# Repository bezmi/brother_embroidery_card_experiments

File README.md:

# Brother embroidery card experiments
I wanted to try and get an old Brother NV500D working with own digitised PES files.

These machines have only got a proprietary memory card slot, which takes brother design cards.

Rewritable cards were available from many manufacturers, including Brother, but they've since mostly fizzled away as the newer machines have USB on board.

This repository is my documentation for a custom design card PCB and software to write images to these cards.

## The PCB
The brother design cards use parallel memory ICs, with 19 address pins and 8 data pins.
My initial experimental PCB is based on the [esp32 PCB done by AeroX2](https://github.com/AeroX2/brother-cart-emulator), but uses a Teensy 3.5 because that's what I had lying around - lots of 5V tolerant GPIO so I didn't need to order shift register/buffer ICs.

### Teensy firmware
The teensy firmware is pretty clunky right now. It's based on AeroX2's nicer esp32 firmware.

## Generating images and programming the flash

This pretty clunky right now because I'm just trying to get it to work and hopefully get a custom program written to create the binary image to be loaded onto the flash.
First, use [AeroX2's image-dumper'](https://github.com/AeroX2/brother-cart-emulator/tree/main/image-dumper) or my modified version of [mlueft's vikant emulator](https://github.com/mlueft/emcr/tree/master/emulators/vikantUltimateBox) to create an `image.bin` from a `PEC` or `PES` file.
Place `image.bin` on a micro SD card (make sure it is named image.bin).

Plug the Teensy into the memory card PCB, and the SD card into the Teensy and issue a "W" command via a serial monitor.
You can use "V" to verify that the file written to the flash chip matches the `image.bin` on the SD card.

**NOTE: DO NOT HAVE THE MEMORY CARD PLUGGED INTO THE MACHINE POWERED ON AT THE SAME TIME AS HAVING THE TEENSY PLUGGED IN AND CONNECTED VIA USB. THIS BOARD CURRENTLY HAS 0 SAFETY GUARANTEES AND YOU WILL POSSIBLY EXPLODE THE TEENSY**

### Using the Vikant software
Unfortunately I haven't got this part working on linux yet, so I begrudgingly boot into Windows until our own software to write to the cards is created.

1. Download and install the old [Vikant Ultimate Box serial port](http://vikant-emb.com/downloads1/UltimateExplorerInstallation.exe) software (the previous link is the direct download. [Go the bottom of this page if it doesn't work.](https://vikant-emb.com/downloads)).
2. Download and install [`com0com`](https://com0com.sourceforge.net/).
3. Edit the `main.py` in the `card_emulator` directory to use one of the COM ports created with com0com (use device manager to figure it out). 
4. Assuming you have python installed, start an administrator command prompt and `cd` to the folder containing `main.py`.
5. Run python `main.py`.
6. Start the UltimateExplorer (Brother) software. It should detect a card on a COM port and let you write files.
7. Copy `image.bin` from the `card_emulator` directory to the microSD card and follow the instructions above to get it written to the memory card.

#### Dirty hacks
Eventually, there will be a direct pipeline from PES file -> python -> directly written to the flash memory.
At the moment, I have just edited mlueft's code to create a 512K data file to match our flash chip.
Vikant still thinks it's a 1024K chip, so if you write more than 512K worth of data, it will cause issues.

## Experiments
I am trying to figure out the format of the binary data written to the brother embroidery card.
[This EEVblog forum post](https://www.eevblog.com/forum/reviews/brother-(possibly-also-bernina)-embroidery-machine-memory-cards/) was very helpful and is what initially introduced me to AeroX2's stuff. There is a wealth of information in that thread.

The `experiments.ipynb` jupyter notebook contains an interactive plotting routine that will go through the `image.bin` file and plot the data as a bitmap. I did this to figure out where and what thumbnails are stored on the card.

The stitch data is stored at the very end of the card, with thumbnails for the embroidery patterns stored before that.

There are also many random thumbnails in lots of languages for UI elements. It appears that the embroidery card also stores the UI for anything inside the "design card menu" from the LCD screen of the machine - probably thanks to the limited storage these old machines had.

Many of the elements of a standard PEC file are present in this file, but the order is different.

The main thing we need to figure out is where the values which point to the start of the stitch data and thumbnails for each PES file written to the card are stored.

# Reverse engineering the file structure
See [notes.org](notes.org)

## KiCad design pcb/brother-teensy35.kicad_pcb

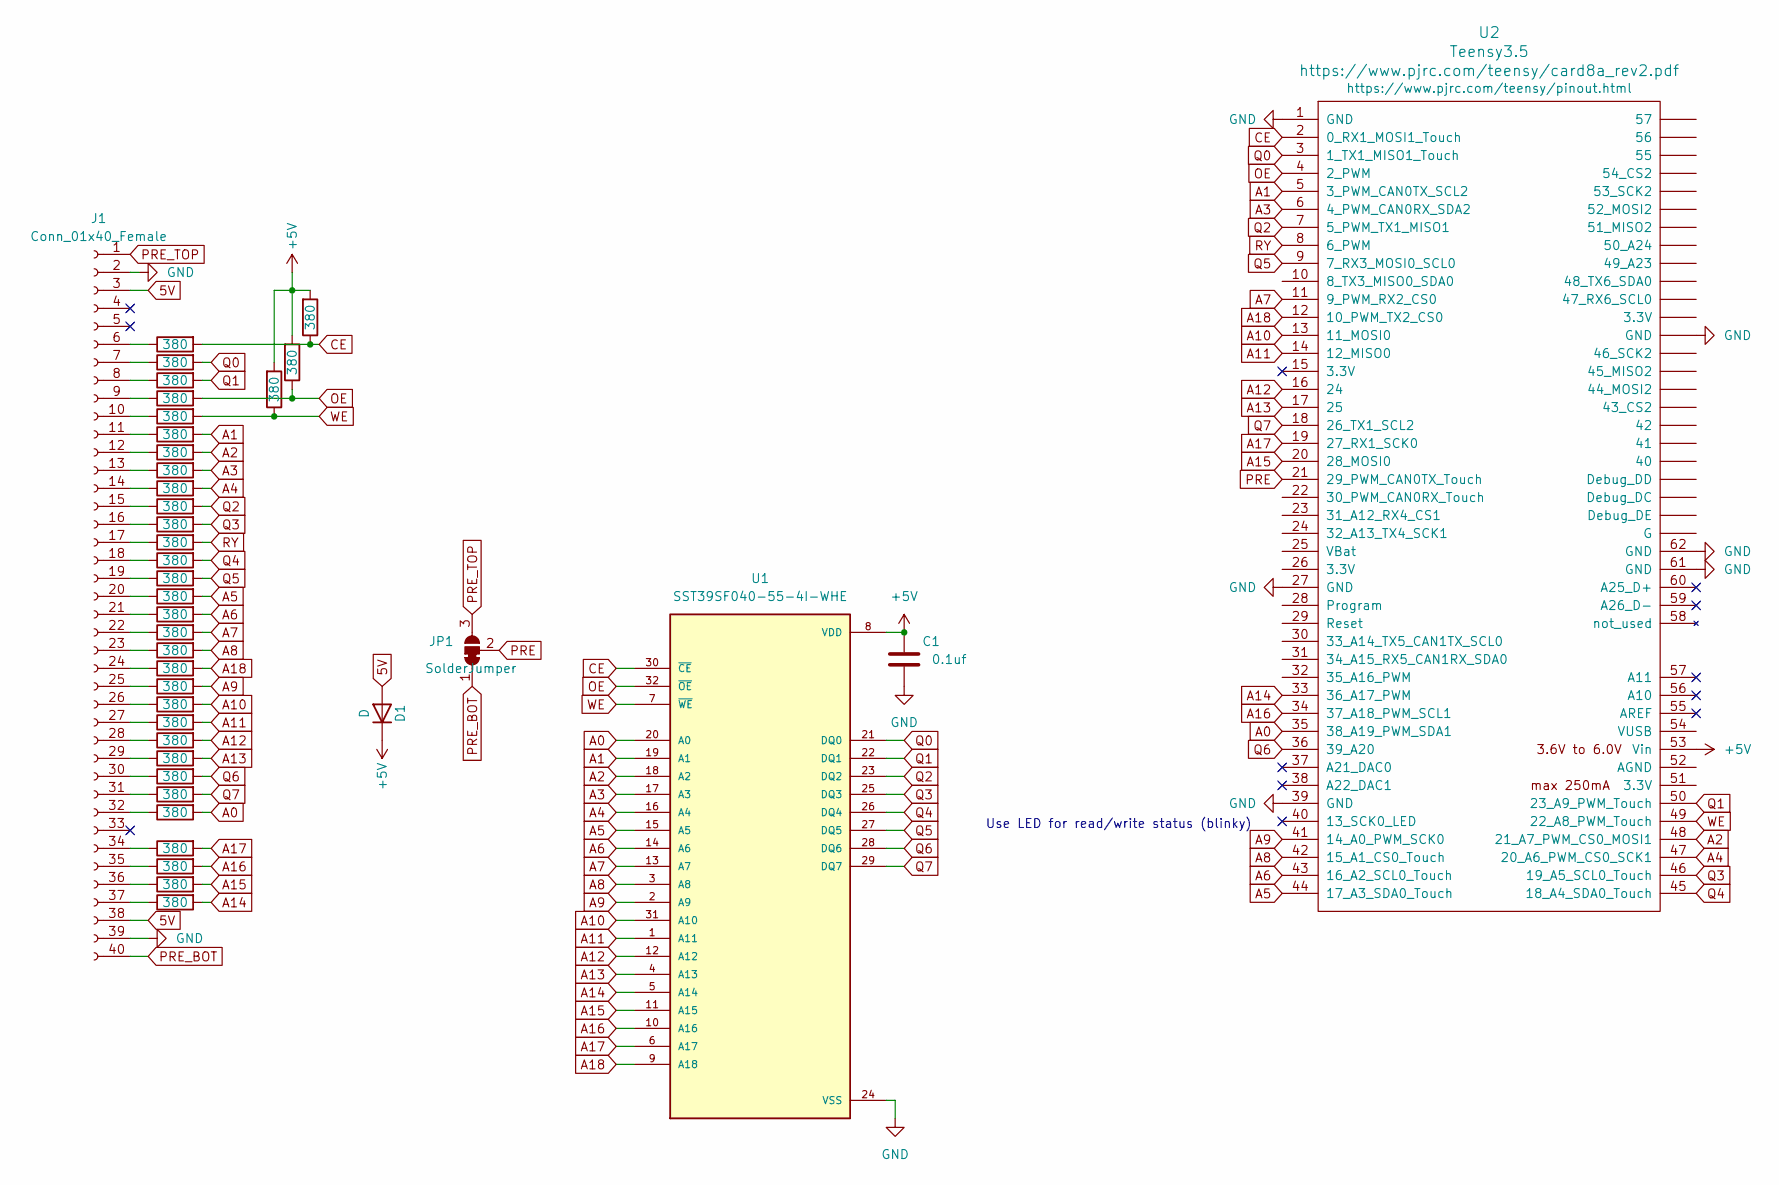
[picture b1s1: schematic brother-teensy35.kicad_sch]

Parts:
C1: 0.1uf; C_0603_1608Metric_Pad1.08x0.95mm_HandSolder
D1: D; D_SOD-323_HandSoldering
J1: Conn_01x40_Female; PinHeader_1x40_SMD
JP1: SolderJumper; SolderJumper-3_P1.3mm_Bridged12_Pad1.0x1.5mm
R1, R2, R3, R4, R5, R6, R7, R8, R9, R10, R11, R12, R13, R14, R15, R16, R17, R18, R19, R20, R21, R22, R23, R24, R25, R26, R27, R28, R29, R30, R31, R32, R33, R34: 380; R_0603_1608Metric_Pad0.98x0.95mm_HandSolder
U1: SST39SF040-55-4I-WHE; SOP50P1400X120-32N; PARTREV C
U2: Teensy3.5; Teensy35_36

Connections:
5V: D1.2 (A), J1.3, J1.38
+5V: C1.2, D1.1 (K), R32.2, R33.2, R34.2, U1.8 (VDD), U2.53 (Vin)
A0: R27.2, U1.20 (A0), U2.35 (38_A19_PWM_SDA1)
A1: R6.2, U1.19 (A1), U2.5 (3_PWM_CAN0TX_SCL2)
A2: R7.2, U1.18 (A2), U2.48 (21_A7_PWM_CS0_MOSI1)
A3: R8.2, U1.17 (A3), U2.6 (4_PWM_CAN0RX_SDA2)
A4: R9.2, U1.16 (A4), U2.47 (20_A6_PWM_CS0_SCK1)
A5: R15.2, U1.15 (A5), U2.44 (17_A3_SDA0_Touch)
A6: R16.2, U1.14 (A6), U2.43 (16_A2_SCL0_Touch)
A7: R17.2, U1.13 (A7), U2.11 (9_PWM_RX2_CS0)
A8: R18.2, U1.3 (A8), U2.42 (15_A1_CS0_Touch)
A9: R20.2, U1.2 (A9), U2.41 (14_A0_PWM_SCK0)
A10: R21.2, U1.31 (A10), U2.13 (11_MOSI0)
A11: R22.2, U1.1 (A11), U2.14 (12_MISO0)
A12: R23.2, U1.12 (A12), U2.16 (24)
A13: R24.2, U1.4 (A13), U2.17 (25)
A14: R31.2, U1.5 (A14), U2.33 (36_A17_PWM)
A15: R30.2, U1.11 (A15), U2.20 (28_MOSI0)
A16: R29.2, U1.10 (A16), U2.34 (37_A18_PWM_SCL1)
A17: R28.2, U1.6 (A17), U2.19 (27_RX1_SCK0)
A18: R19.2, U1.9 (A18), U2.12 (10_PWM_TX2_CS0)
CE: R1.2, R34.1, U1.30 (~CE), U2.2 (0_RX1_MOSI1_Touch)
GND: C1.1, J1.2, J1.39, U1.24 (VSS), U2.1 (GND), U2.27 (GND), U2.39 (GND), U2.61 (GND), U2.62 (GND), U2.~ (3.3V)
unnamed: J1.6, R1.1
unnamed: J1.7, R2.1
unnamed: J1.8, R3.1
unnamed: J1.9, R4.1
unnamed: J1.10, R5.1
unnamed: J1.11, R6.1
unnamed: J1.12, R7.1
unnamed: J1.13, R8.1
unnamed: J1.14, R9.1
unnamed: J1.15, R10.1
unnamed: J1.16, R11.1
unnamed: J1.17, R12.1
unnamed: J1.18, R13.1
unnamed: J1.19, R14.1
unnamed: J1.20, R15.1
unnamed: J1.21, R16.1
unnamed: J1.22, R17.1
unnamed: J1.23, R18.1
unnamed: J1.24, R19.1
unnamed: J1.25, R20.1
unnamed: J1.26, R21.1
unnamed: J1.27, R22.1
unnamed: J1.28, R23.1
unnamed: J1.29, R24.1
unnamed: J1.30, R25.1
unnamed: J1.31, R26.1
unnamed: J1.32, R27.1
unnamed: J1.34, R28.1
unnamed: J1.35, R29.1
unnamed: J1.36, R30.1
unnamed: J1.37, R31.1
OE: R4.2, R33.1, U1.32 (~OE), U2.4 (2_PWM)
PRE: JP1.2 (C), U2.21 (29_PWM_CAN0TX_Touch)
PRE_BOT: J1.40, JP1.1 (A)
PRE_TOP: J1.1, JP1.3 (B)
Q0: R2.2, U1.21 (DQ0), U2.3 (1_TX1_MISO1_Touch)
Q1: R3.2, U1.22 (DQ1), U2.50 (23_A9_PWM_Touch)
Q2: R10.2, U1.23 (DQ2), U2.7 (5_PWM_TX1_MISO1)
Q3: R11.2, U1.25 (DQ3), U2.46 (19_A5_SCL0_Touch)
Q4: R13.2, U1.26 (DQ4), U2.45 (18_A4_SDA0_Touch)
Q5: R14.2, U1.27 (DQ5), U2.9 (7_RX3_MOSI0_SCL0)
Q6: R25.2, U1.28 (DQ6), U2.36 (39_A20)
Q7: R26.2, U1.29 (DQ7), U2.18 (26_TX1_SCL2)
RY: R12.2, U2.8 (6_PWM)
WE: R5.2, R32.1, U1.7 (~WE), U2.49 (22_A8_PWM_Touch)

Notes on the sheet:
Use LED for read/write status (blinky)

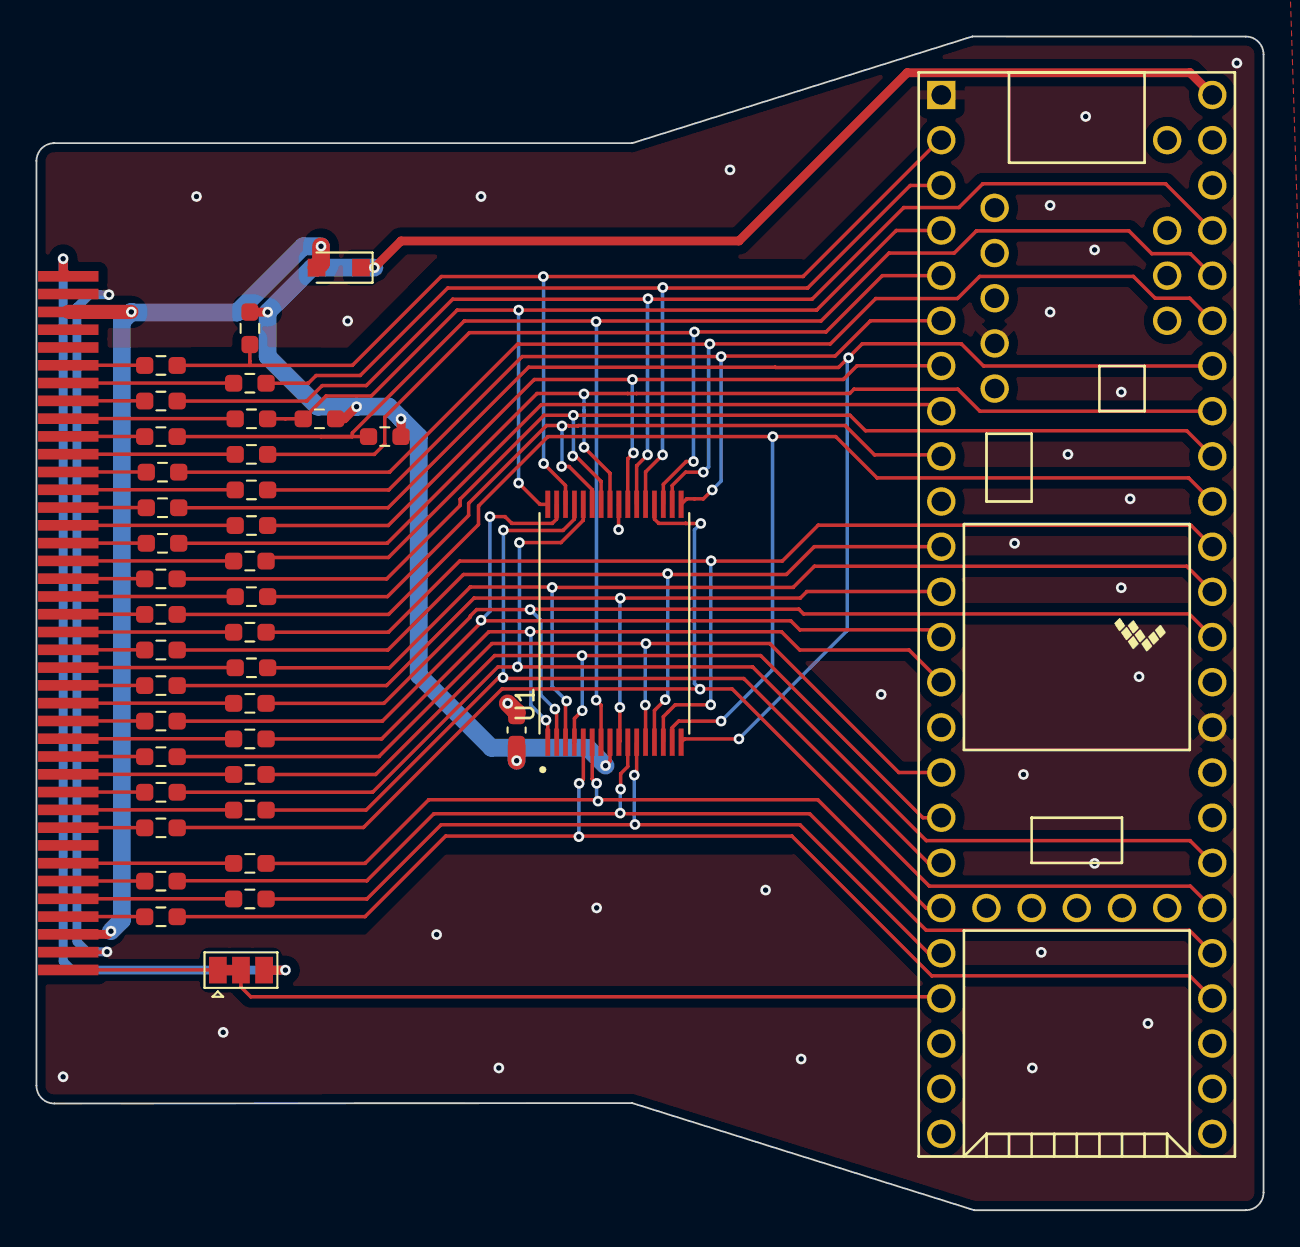
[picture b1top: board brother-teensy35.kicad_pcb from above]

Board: 2 copper layers, 69.0 x 66.0 mm, 40 parts (0 on the bottom side), 68 nets.

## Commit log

2023-03-10 add notes, progress on decoding the file structure
2023-03-11 Update notes.org
    started going through PED basic to reverse engineer and confirm current notes
